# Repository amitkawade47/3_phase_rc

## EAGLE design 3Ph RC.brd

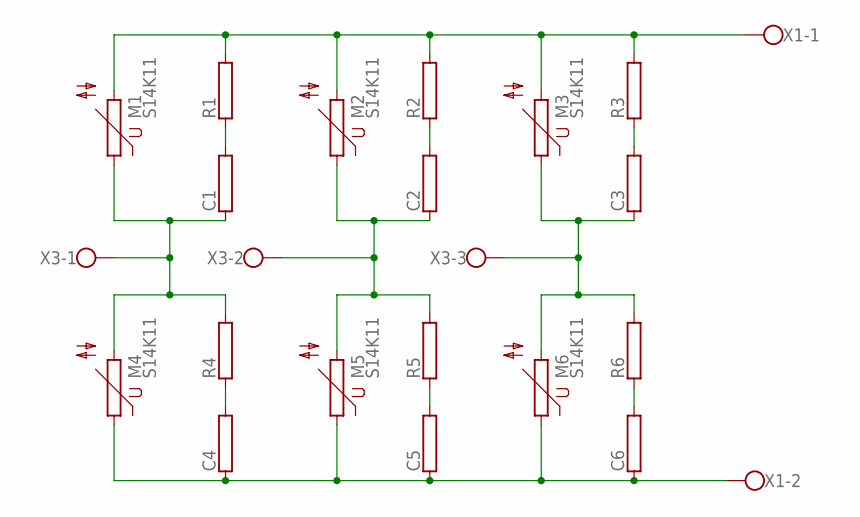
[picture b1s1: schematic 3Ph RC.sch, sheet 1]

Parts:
C1, C2, C3, C4, C5, C6: RRWM8X34; RWM8X34
M1, M2, M3, M4, M5, M6: S14K11
R1, R2, R3, R4, R5, R6: RRWM10X45; RWM10X45
X1: W237-102
X3: W237-103

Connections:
C1: C1.2, R1.1
unnamed: M1.2, M2.2, M3.2, R1.2, R2.2, R3.2, X1.1
unnamed: C2.1, M2.1, M5.2, R5.2, X3.2
unnamed: C2.2, R2.1
unnamed: C3.2, R3.1
unnamed: C1.1, M1.1, M4.2, R4.2, X3.1
unnamed: C3.1, M3.1, M6.2, R6.2, X3.3
unnamed: C6.2, R6.1
unnamed: C4.1, C5.1, C6.1, M4.1, M5.1, M6.1, X1.2
unnamed: C4.2, R4.1
unnamed: C5.2, R5.1

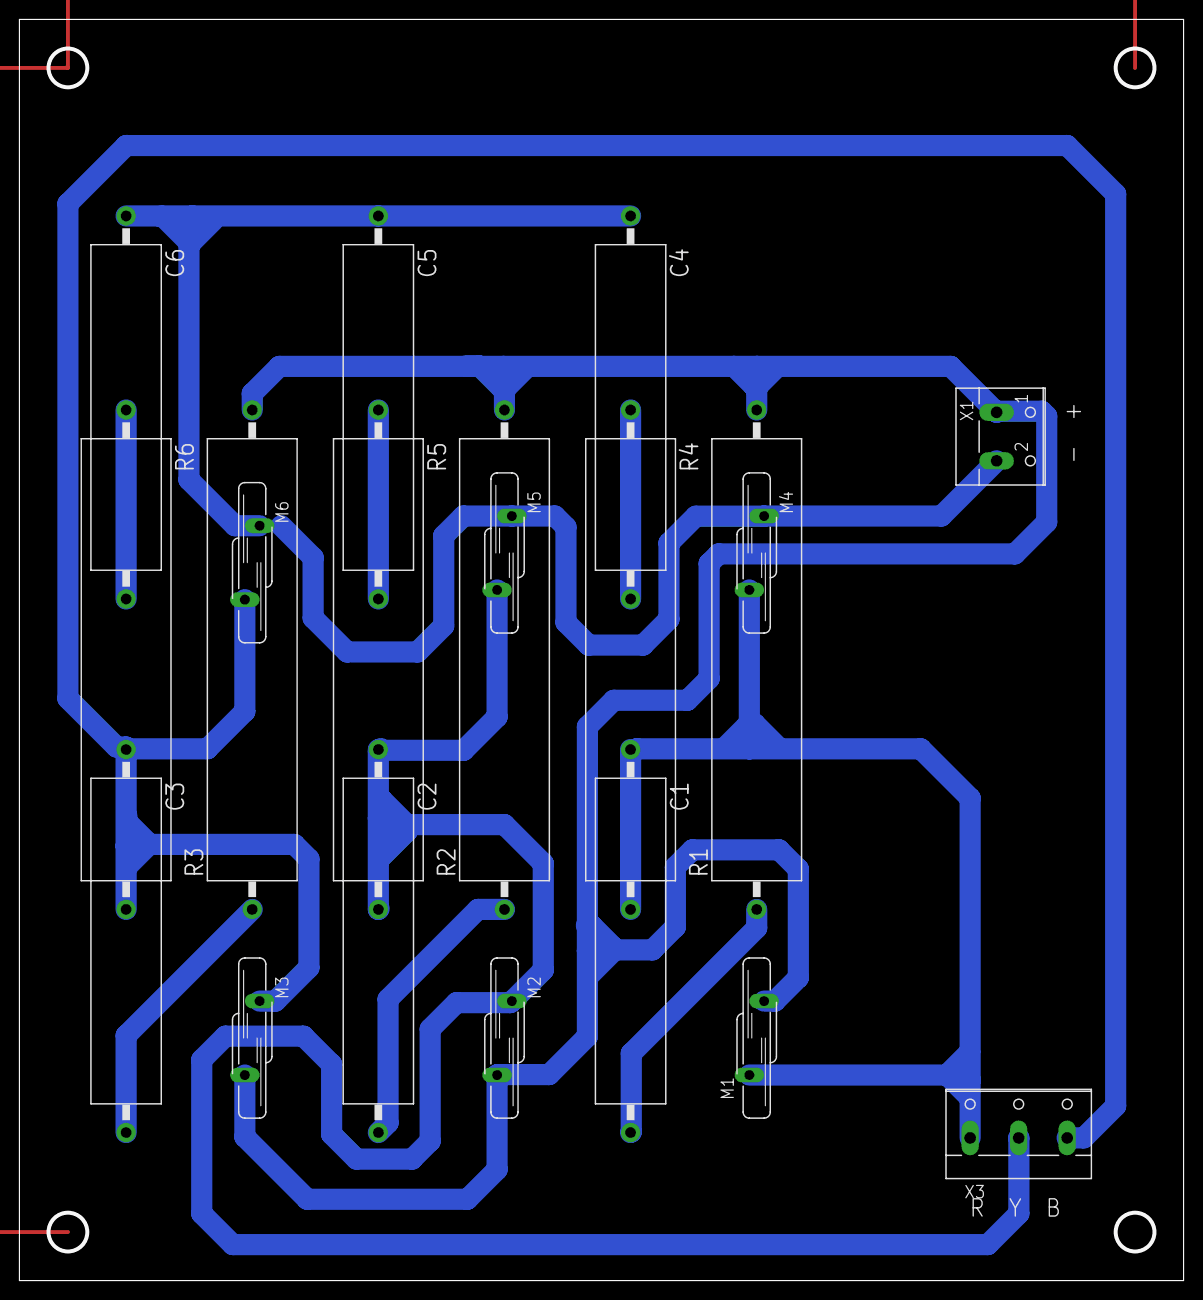
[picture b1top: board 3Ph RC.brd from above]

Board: 2 copper layers, 120.0 x 130.0 mm, 20 parts (0 on the bottom side), 11 nets.

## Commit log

2018-03-11 PCB design done
    just added to git for backup
2018-03-11 pdf removed
    assembly pdf removed
